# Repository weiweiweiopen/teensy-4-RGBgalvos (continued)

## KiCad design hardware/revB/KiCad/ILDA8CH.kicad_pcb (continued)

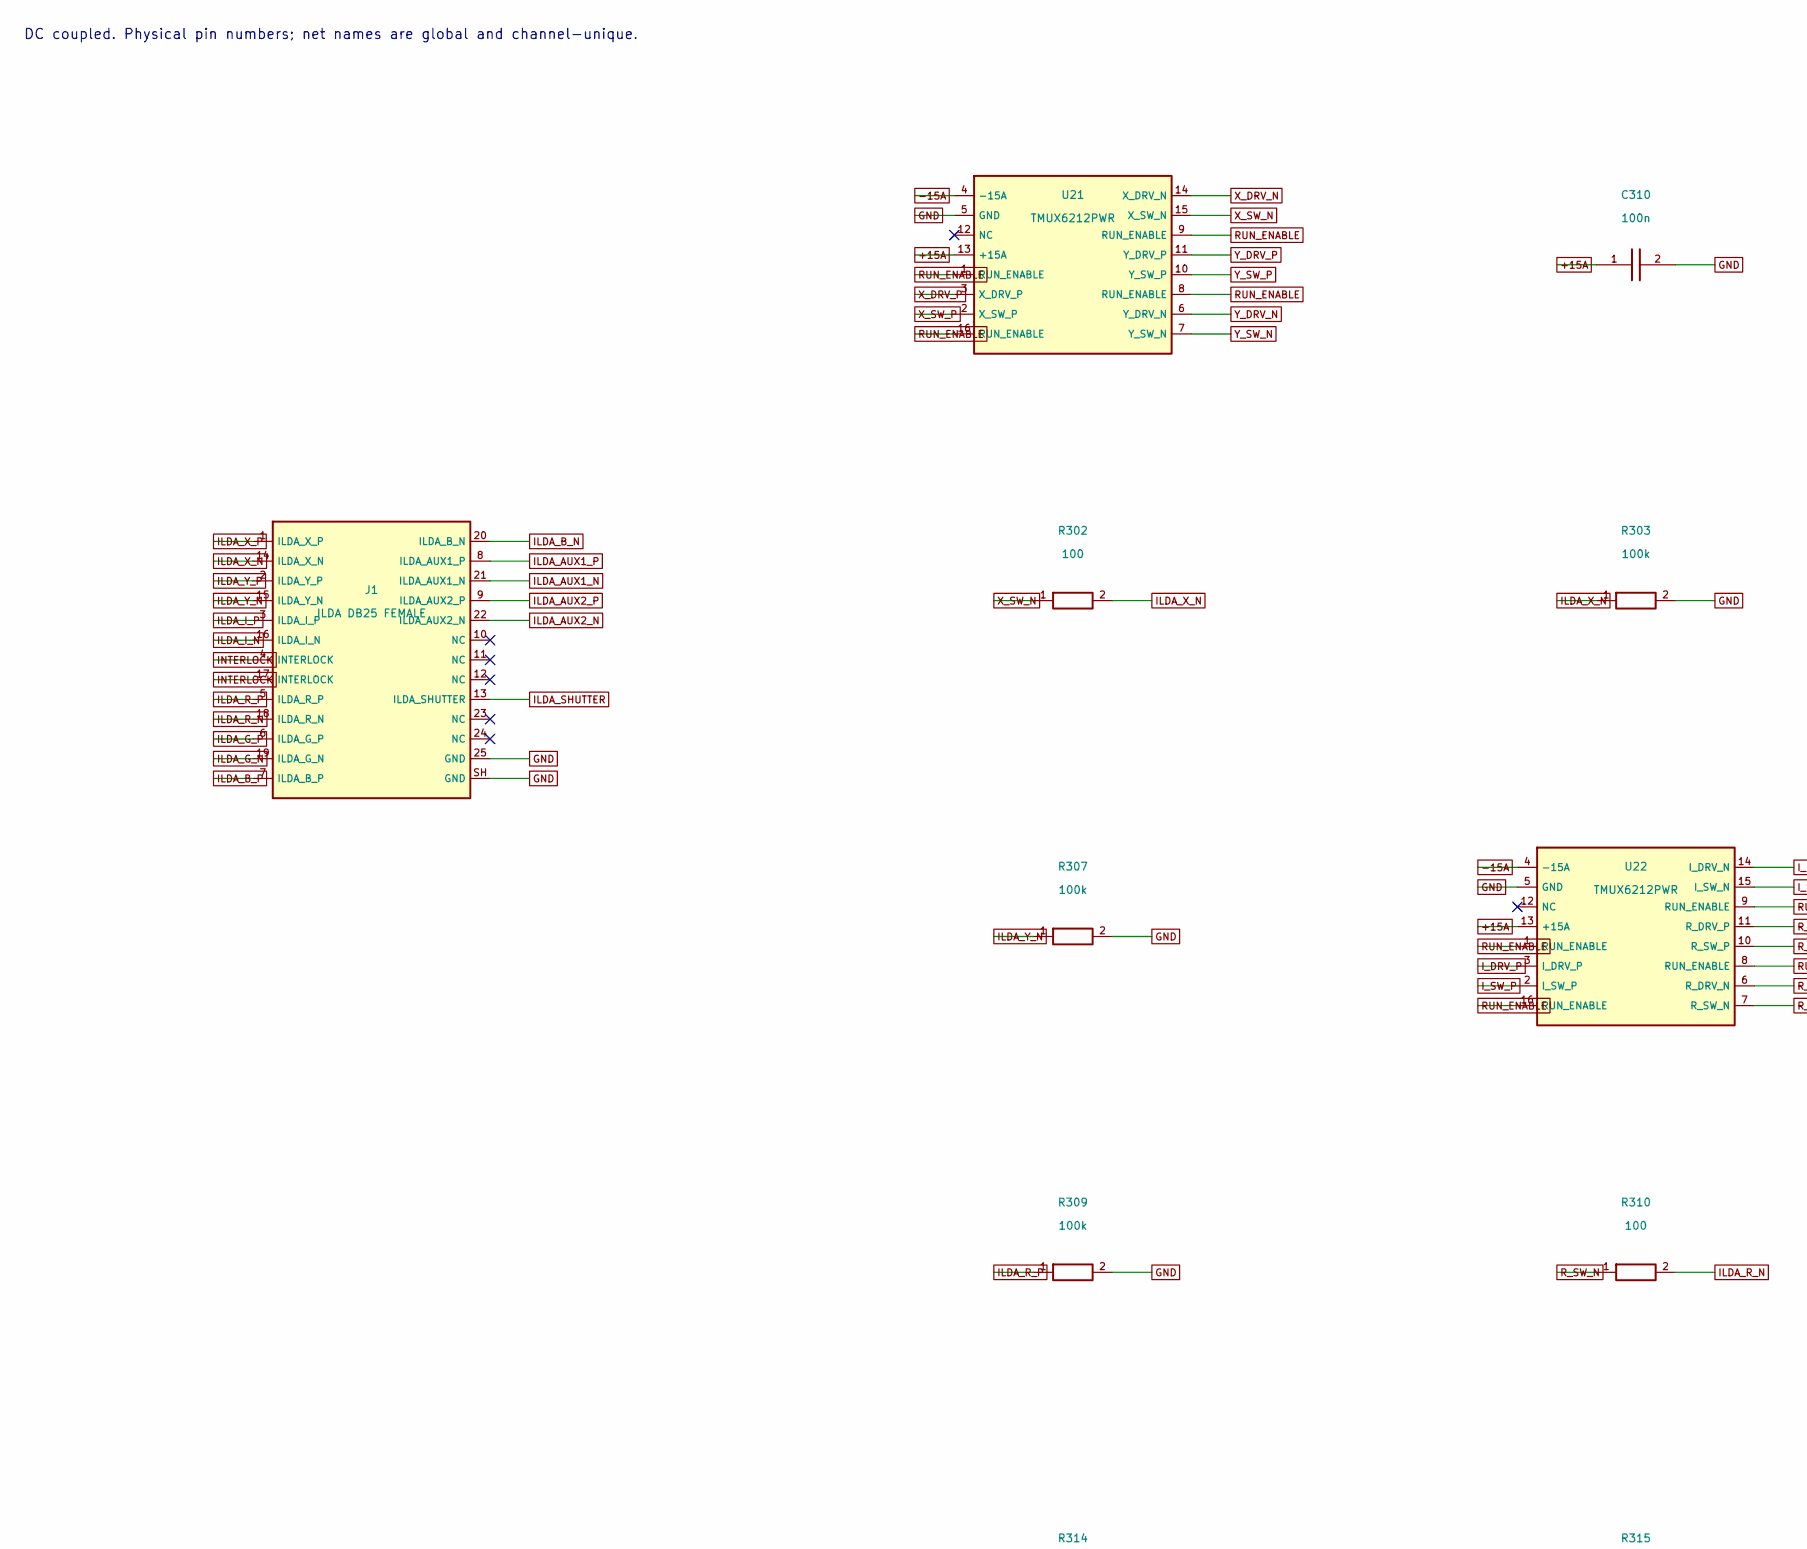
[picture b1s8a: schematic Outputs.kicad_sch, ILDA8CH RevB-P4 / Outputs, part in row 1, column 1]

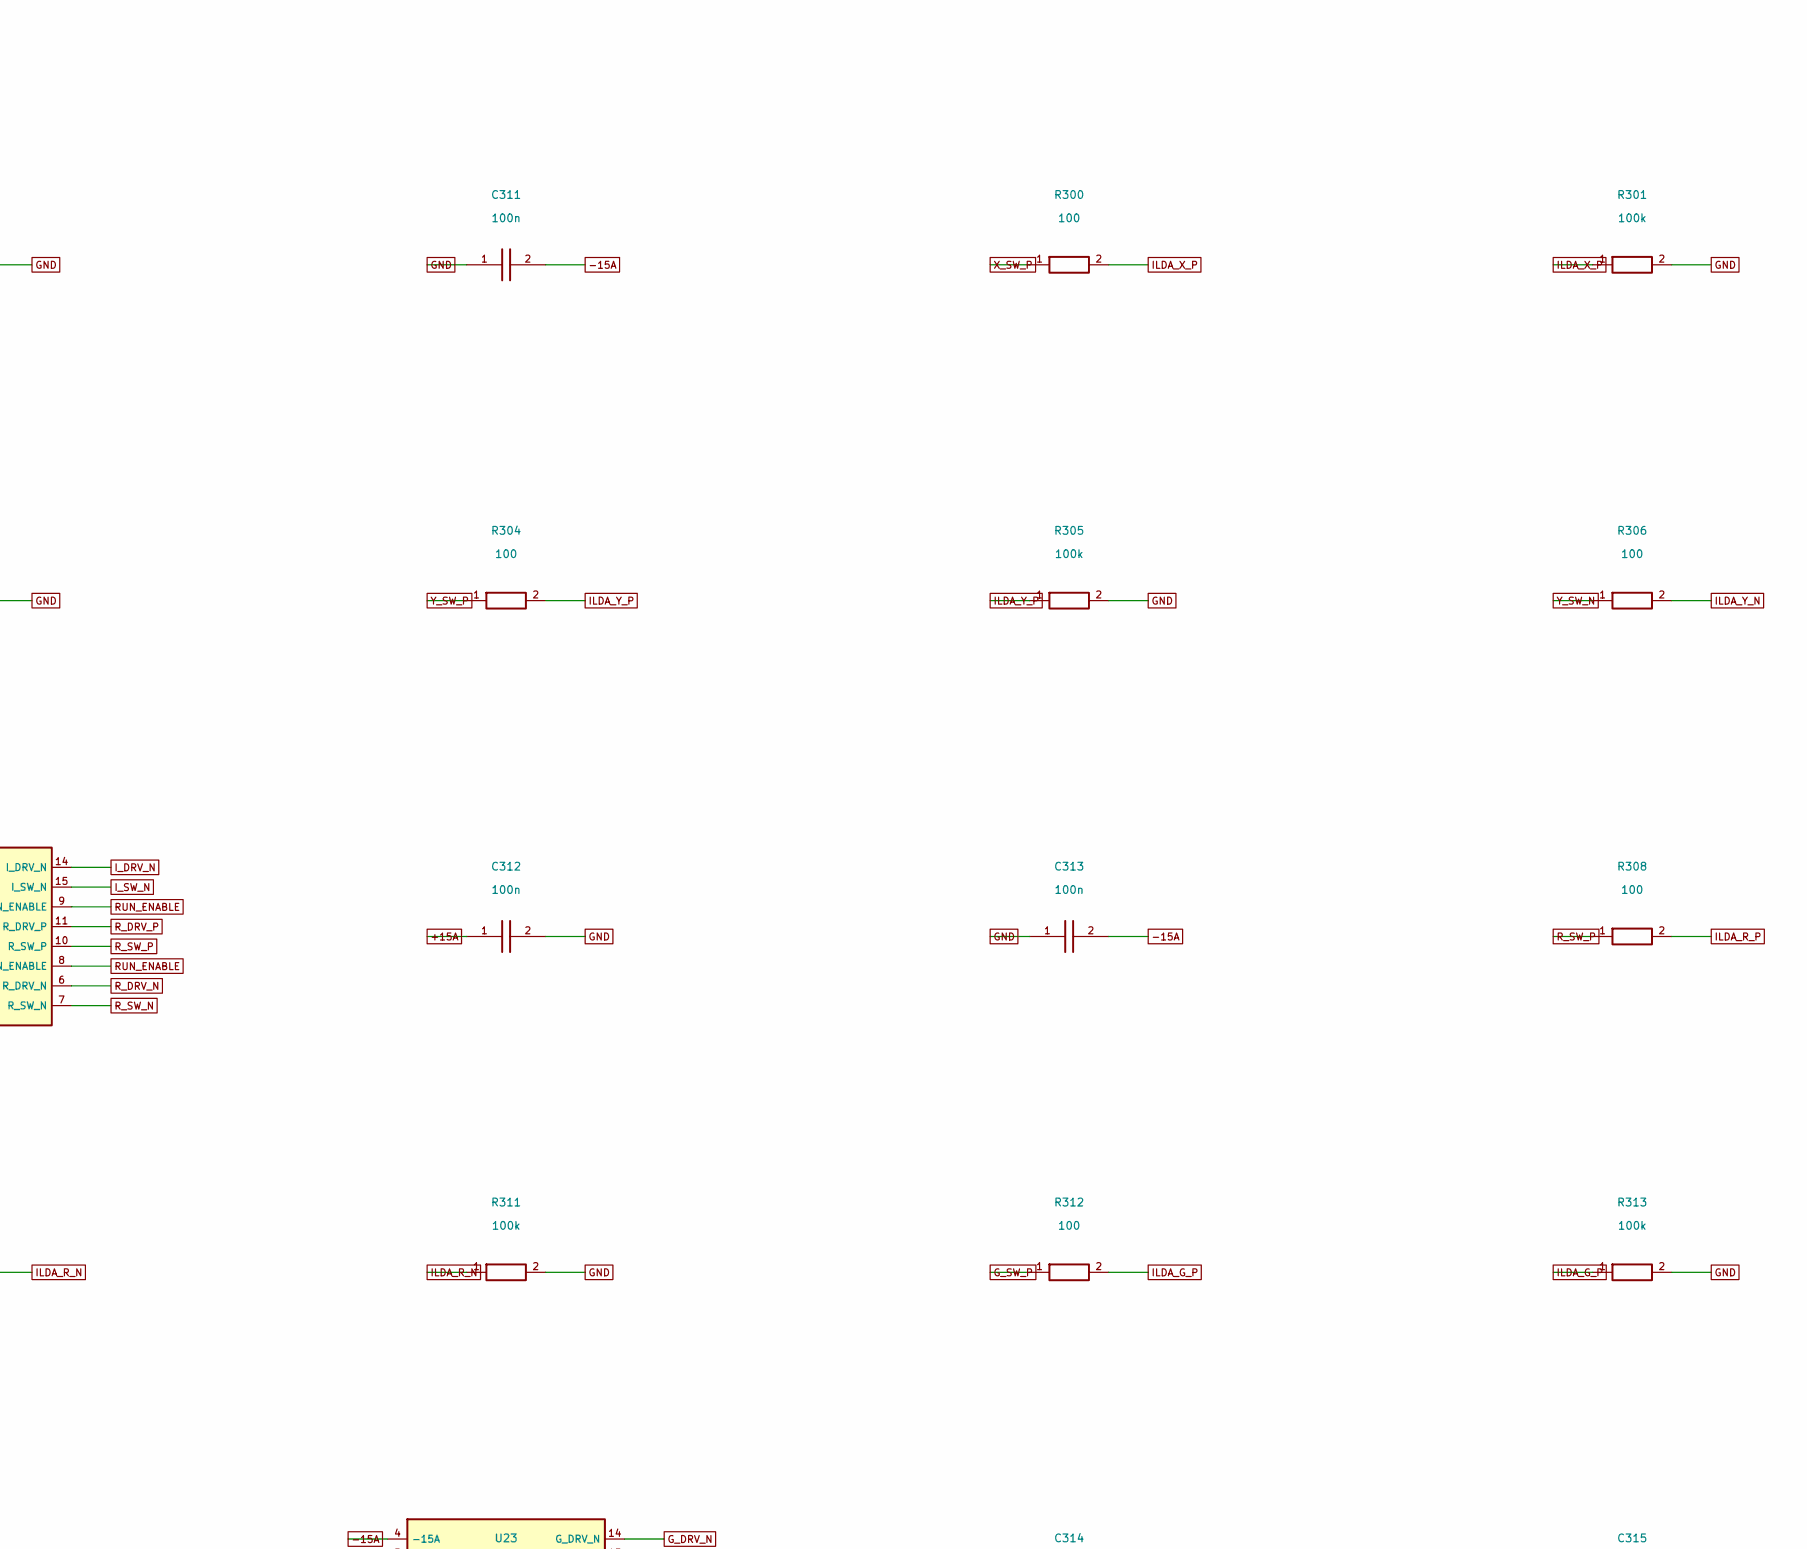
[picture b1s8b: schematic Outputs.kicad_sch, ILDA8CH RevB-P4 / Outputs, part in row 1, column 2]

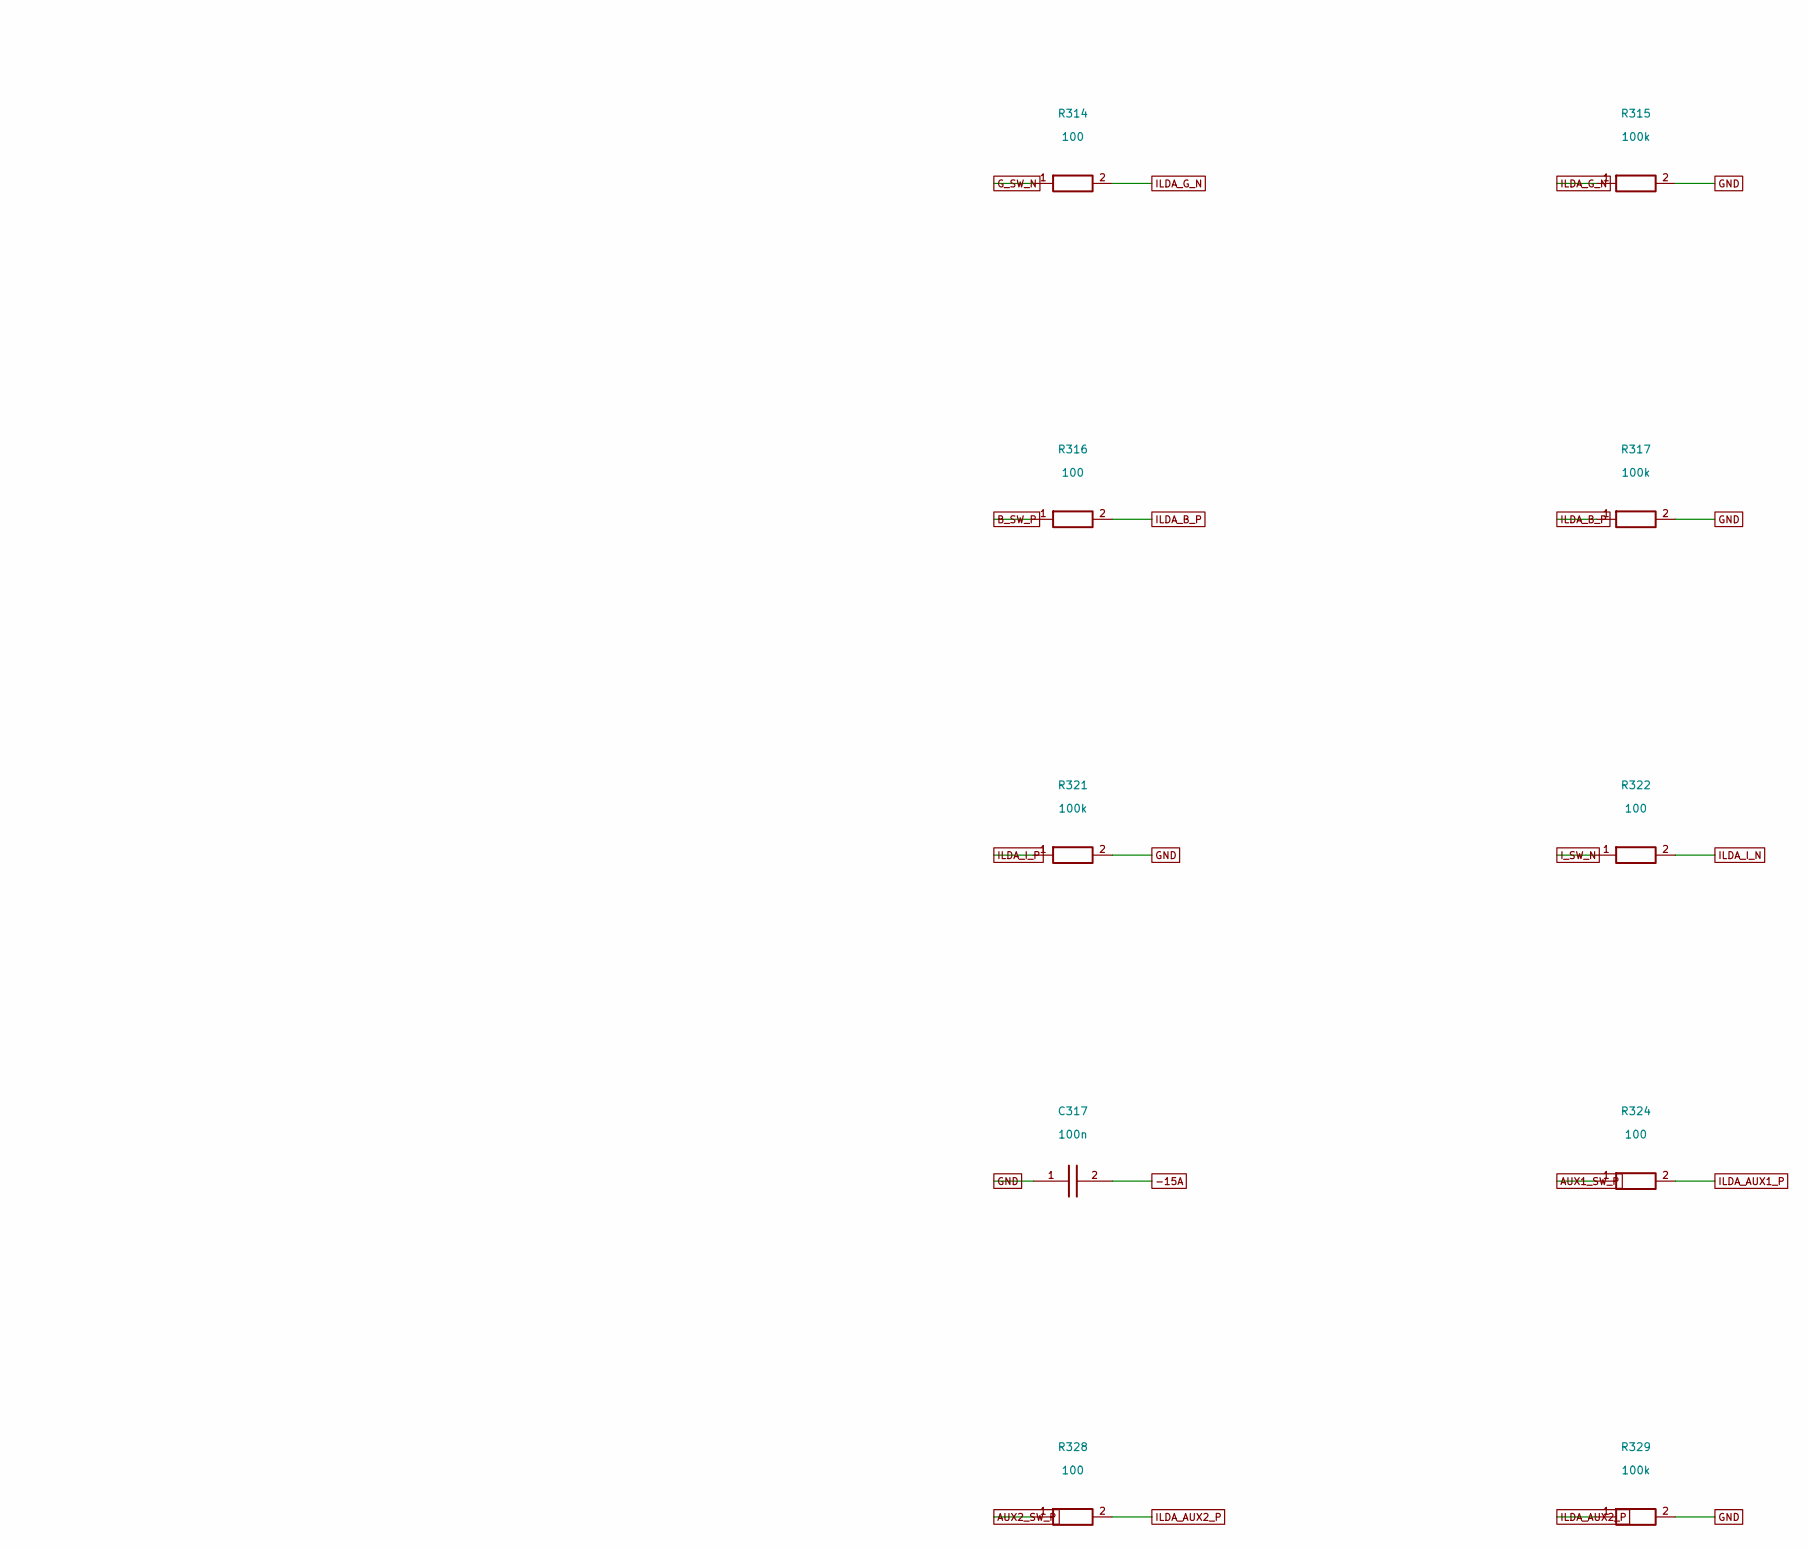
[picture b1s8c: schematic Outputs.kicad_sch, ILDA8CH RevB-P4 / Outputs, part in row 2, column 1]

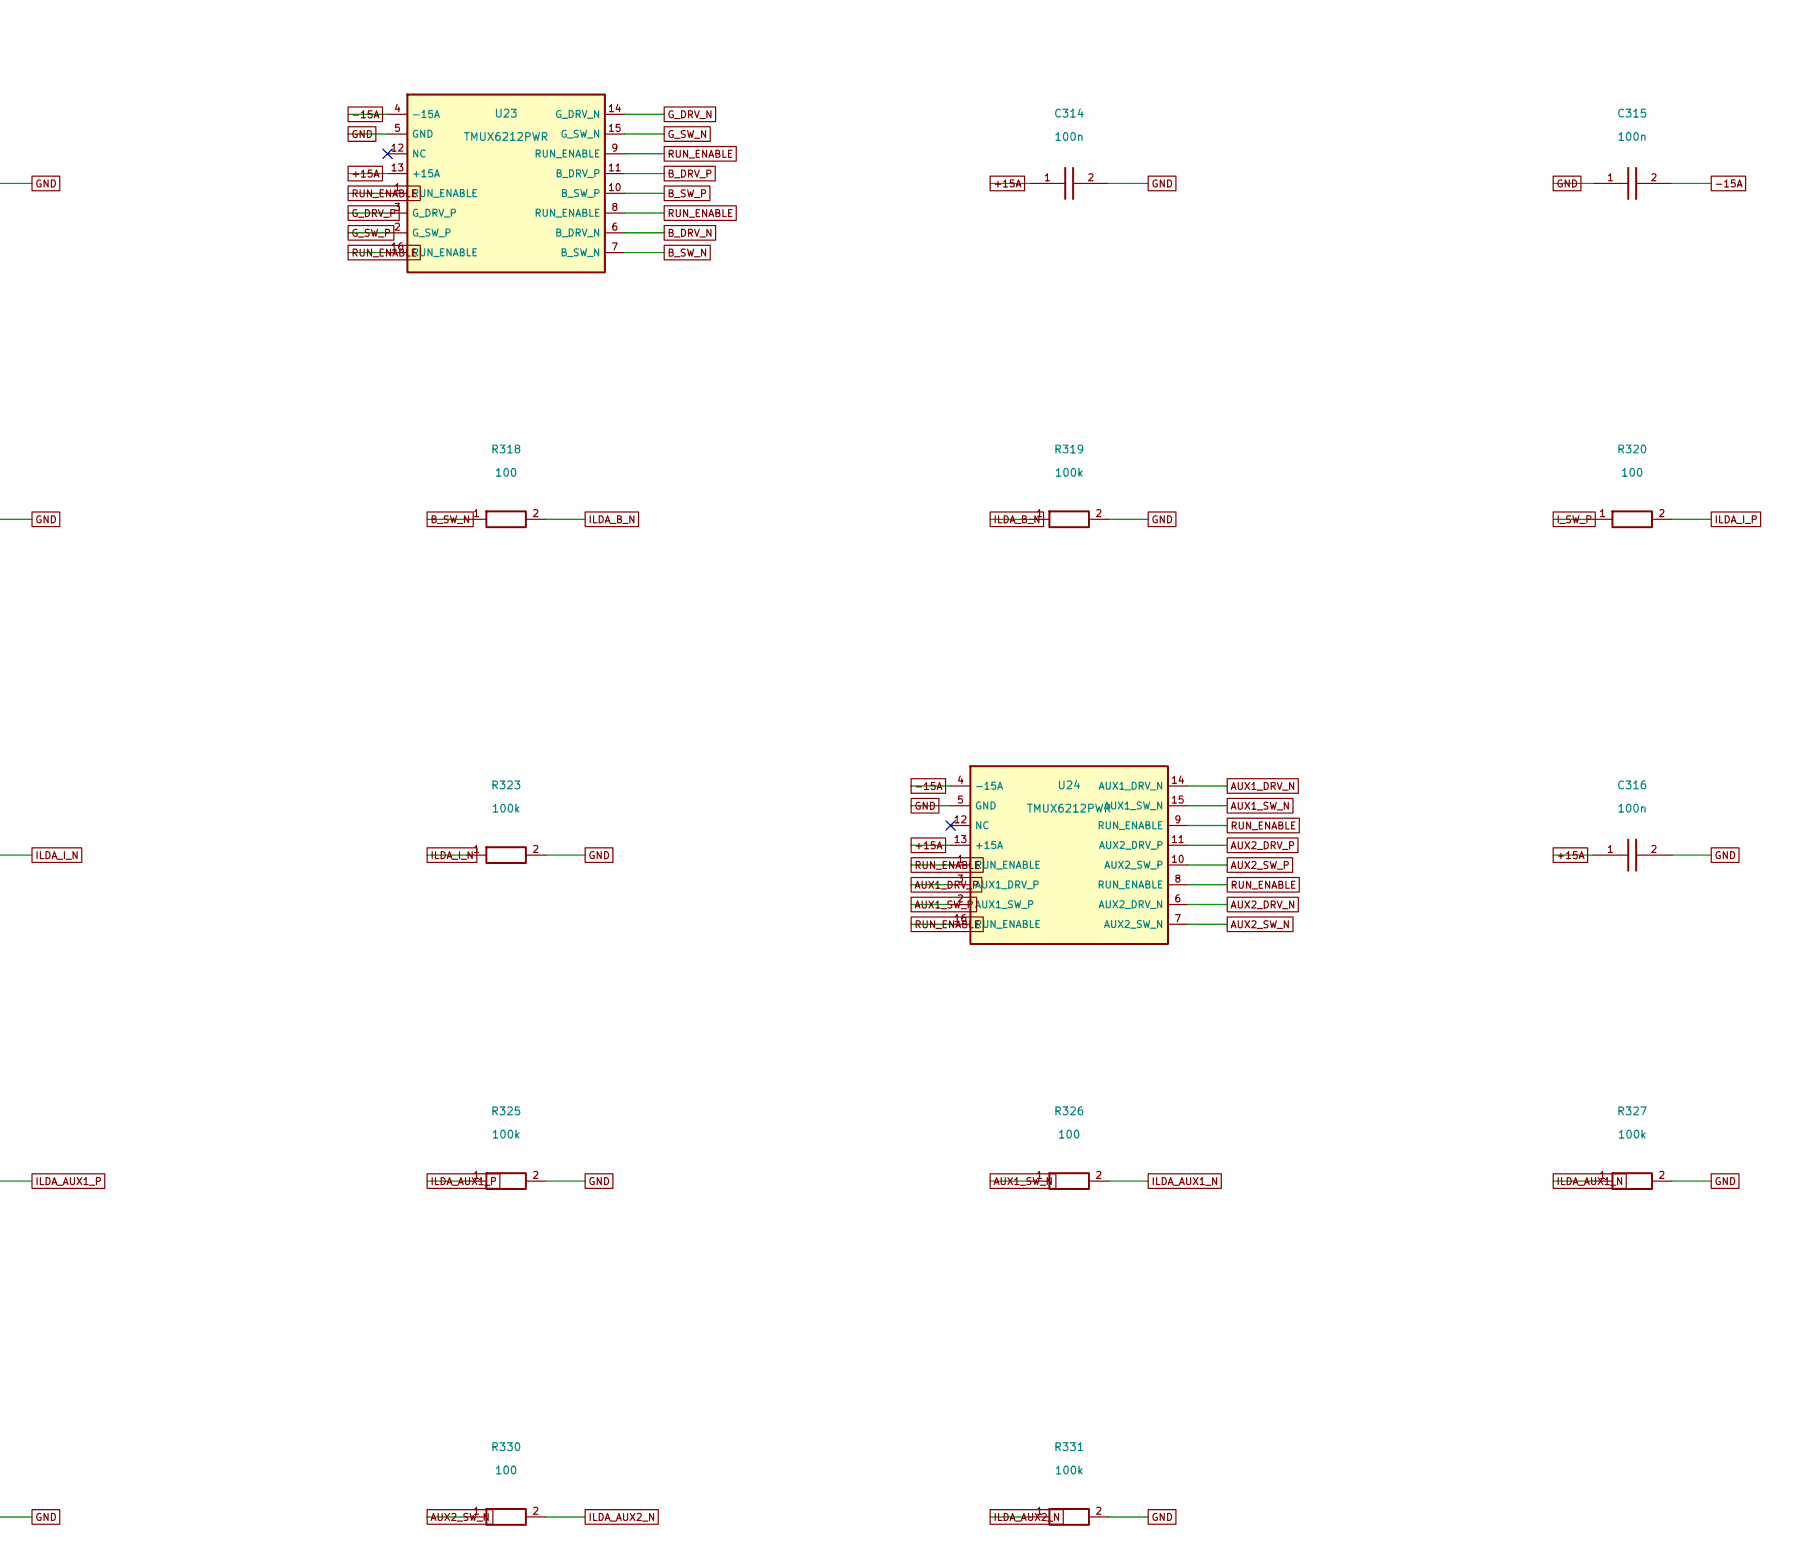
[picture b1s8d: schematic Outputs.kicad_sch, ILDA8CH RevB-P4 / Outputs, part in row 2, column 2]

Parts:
C310, C311, C312, C313, C314, C315, C316, C317: 100n; Capacitor_SMD__C_0603_1608Metric; MPN GRM188R71H104KA93D; LCSC C77055
J1: ILDA DB25 FEMALE; Connector_Dsub__DSUB-25_Socket_Horizontal_P2.77x2.84mm_Edge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; MPN CANDIDATE: RA DB25 female, 7.70mm pin/e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
R300, R302, R304, R306, R308, R310, R312, R314, R316, R318, R320, R322, R324, R326, R328, R330: 100; Resistor_SMD__R_2512_6332Metric; MPN RC2512FK-07100RL; LCSC C309603
R301, R303, R305, R307, R309, R311, R313, R315, R317, R319, R321, R323, R325, R327, R329, R331: 100k; Resistor_SMD__R_0603_1608Metric; MPN RC0603FR-07100KL; LCSC C14675
U21, U22, U23, U24: TMUX6212PWR; Package_SO__TSSOP-16_4.4x5mm_P0.65mm; MPN TMUX6212PWR; LCSC C2902526

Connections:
+15A: C310.1, C312.1, C314.1, C316.1, U21.13 (+15A), U22.13 (+15A), U23.13 (+15A), U24.13 (+15A); also elsewhere on the board
-15A: C311.2, C313.2, C315.2, C317.2, U21.4 (-15A), U22.4 (-15A), U23.4 (-15A), U24.4 (-15A); also elsewhere on the board
AUX1_DRV_N: U24.14 (AUX1_DRV_N); also elsewhere on the board
AUX1_DRV_P: U24.3 (AUX1_DRV_P); also elsewhere on the board
AUX1_SW_N: R326.1, U24.15 (AUX1_SW_N)
AUX1_SW_P: R324.1, U24.2 (AUX1_SW_P)
AUX2_DRV_N: U24.6 (AUX2_DRV_N); also elsewhere on the board
AUX2_DRV_P: U24.11 (AUX2_DRV_P); also elsewhere on the board
AUX2_SW_N: R330.1, U24.7 (AUX2_SW_N)
AUX2_SW_P: R328.1, U24.10 (AUX2_SW_P)
B_DRV_N: U23.6 (B_DRV_N); also elsewhere on the board
B_DRV_P: U23.11 (B_DRV_P); also elsewhere on the board
B_SW_N: R318.1, U23.7 (B_SW_N)
B_SW_P: R316.1, U23.10 (B_SW_P)
GND: C310.2, C311.1, C312.2, C313.1, C314.2, C315.1, C316.2, C317.1, J1.25 (GND), J1.SH (GND), R301.2, R303.2, R305.2, R307.2, R309.2, R311.2, R313.2, R315.2, R317.2, R319.2, R321.2, R323.2, R325.2, R327.2, R329.2, R331.2, U21.5 (GND), U22.5 (GND), U23.5 (GND), U24.5 (GND); also elsewhere on the board
G_DRV_N: U23.14 (G_DRV_N); also elsewhere on the board
G_DRV_P: U23.3 (G_DRV_P); also elsewhere on the board
G_SW_N: R314.1, U23.15 (G_SW_N)
G_SW_P: R312.1, U23.2 (G_SW_P)
ILDA_AUX1_N: J1.21 (ILDA_AUX1_N), R326.2, R327.1
ILDA_AUX1_P: J1.8 (ILDA_AUX1_P), R324.2, R325.1
ILDA_AUX2_N: J1.22 (ILDA_AUX2_N), R330.2, R331.1
ILDA_AUX2_P: J1.9 (ILDA_AUX2_P), R328.2, R329.1
ILDA_B_N: J1.20 (ILDA_B_N), R318.2, R319.1
ILDA_B_P: J1.7 (ILDA_B_P), R316.2, R317.1
ILDA_G_N: J1.19 (ILDA_G_N), R314.2, R315.1
ILDA_G_P: J1.6 (ILDA_G_P), R312.2, R313.1
ILDA_I_N: J1.16 (ILDA_I_N), R322.2, R323.1
ILDA_I_P: J1.3 (ILDA_I_P), R320.2, R321.1
ILDA_R_N: J1.18 (ILDA_R_N), R310.2, R311.1
ILDA_R_P: J1.5 (ILDA_R_P), R308.2, R309.1
ILDA_SHUTTER: J1.13 (ILDA_SHUTTER); also elsewhere on the board
ILDA_X_N: J1.14 (ILDA_X_N), R302.2, R303.1
ILDA_X_P: J1.1 (ILDA_X_P), R300.2, R301.1
ILDA_Y_N: J1.15 (ILDA_Y_N), R306.2, R307.1
ILDA_Y_P: J1.2 (ILDA_Y_P), R304.2, R305.1
INTERLOCK: J1.4 (INTERLOCK), J1.17 (INTERLOCK)
I_DRV_N: U22.14 (I_DRV_N); also elsewhere on the board
I_DRV_P: U22.3 (I_DRV_P); also elsewhere on the board
I_SW_N: R322.1, U22.15 (I_SW_N)
I_SW_P: R320.1, U22.2 (I_SW_P)
RUN_ENABLE: U21.1 (RUN_ENABLE), U21.8 (RUN_ENABLE), U21.9 (RUN_ENABLE), U21.16 (RUN_ENABLE), U22.1 (RUN_ENABLE), U22.8 (RUN_ENABLE), U22.9 (RUN_ENABLE), U22.16 (RUN_ENABLE), U23.1 (RUN_ENABLE), U23.8 (RUN_ENABLE), U23.9 (RUN_ENABLE), U23.16 (RUN_ENABLE), U24.1 (RUN_ENABLE), U24.8 (RUN_ENABLE), U24.9 (RUN_ENABLE), U24.16 (RUN_ENABLE); also elsewhere on the board
R_DRV_N: U22.6 (R_DRV_N); also elsewhere on the board
R_DRV_P: U22.11 (R_DRV_P); also elsewhere on the board
R_SW_N: R310.1, U22.7 (R_SW_N)
R_SW_P: R308.1, U22.10 (R_SW_P)
X_DRV_N: U21.14 (X_DRV_N); also elsewhere on the board
X_DRV_P: U21.3 (X_DRV_P); also elsewhere on the board
X_SW_N: R302.1, U21.15 (X_SW_N)
X_SW_P: R300.1, U21.2 (X_SW_P)
Y_DRV_N: U21.6 (Y_DRV_N); also elsewhere on the board
Y_DRV_P: U21.11 (Y_DRV_P); also elsewhere on the board
Y_SW_N: R306.1, U21.7 (Y_SW_N)
Y_SW_P: R304.1, U21.10 (Y_SW_P)

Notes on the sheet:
DC coupled. Physical pin numbers; net names are global and channel-unique.

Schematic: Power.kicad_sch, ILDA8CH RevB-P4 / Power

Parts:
C1, C2, C3, C4, C5: 10u; Capacitor_SMD__C_0805_2012Metric; MPN GRM21BR61E106KA73L; LCSC C84416
C37, C38, C350: 100n; Capacitor_SMD__C_0603_1608Metric; MPN GRM188R71H104KA93D; LCSC C77055
D1, D2: SS14; Diode_SMD__D_SMA; MPN SS14; LCSC C2480
FB1: 600R@100MHz; Inductor_SMD__L_0805_2012Metric; MPN BLM21PG601SN1D; LCSC C41556732
FID1, FID2, FID3: FIDUCIAL; Fiducial__Fiducial_1mm_Mask2mm
H1, H2, H3, H4: M3 NPTH; MountingHole__MountingHole_3.2mm_M3
J2: Molex KK-254 3P +/-15V; Connector_Molex__Molex_KK-254_AE-6410-03A_1x03_P2.54mm_Vert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; MPN 22-27-2031
R23, R25, R352, R354, R357, R358, R360, R369, R370: 100k; Resistor_SMD__R_0603_1608Metric; MPN RC0603FR-07100KL; LCSC C14675
R24: 20k; Resistor_SMD__R_0603_1608Metric; MPN RT0603BRD0720KL; LCSC C723637
R26: 10k; Resistor_SMD__R_0603_1608Metric; MPN RT0603BRD0710KL; LCSC C95204
R350, R356: 1M; Resistor_SMD__R_0603_1608Metric; MPN RC0603FR-071ML; LCSC C105578
R351: 200k; Resistor_SMD__R_0603_1608Metric; MPN RC0603FR-07200KL; LCSC C105574
R353: 150k; Resistor_SMD__R_0603_1608Metric; MPN RC0603FR-07150KL; LCSC C114660
R355, R361: 10M; Resistor_SMD__R_0603_1608Metric; MPN RC0603FR-0710ML; LCSC C114606
R359: 45.3k; Resistor_SMD__R_0603_1608Metric; MPN RC0603FR-0745K3L; LCSC C245971
R367: 1k; Resistor_SMD__R_0603_1608Metric; MPN RT0603BRD071KL; LCSC C110776
R371, R372: 100; Resistor_SMD__R_0603_1608Metric; MPN RC0603FR-07100RL; LCSC C105588
U2: TLV75533PDBVR; Package_TO_SOT_SMD__SOT-23-5; MPN TLV75533PDBVR; LCSC C404027
U6: TLV3202AIDGKR; TI_DGK0008A_VSSOP8_3x3_P0.65_Land1.4x0.45; MPN TLV3202AIDGKR; LCSC C478075

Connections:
+3V3: C2.1, U2.5 (+3V3); also elsewhere on the board
+5VA: C3.1, FB1.2; also elsewhere on the board
+15A: C4.1, D1.1 (K), R23.1, R350.1; also elsewhere on the board
-15A: C5.2, D2.2 (A), R25.1, R356.1; also elsewhere on the board
GND: C1.2, C2.2, C3.2, C4.2, C5.1, C37.2, C38.2, C350.2, J2.2 (GND), R24.2, R351.2, R354.2, R360.2, R367.2, R369.2, R370.2, U2.2 (GND), U6.4 (GND); also elsewhere on the board
MCU_3V3: R26.2; also elsewhere on the board
N15_IN: D2.1 (K), J2.3 (N15_IN)
NMON: R358.2, U6.6 (IN2-)
NMON_RAW: R356.2, R357.1, R358.1
NREF: R359.2, R360.1, R361.2, U6.5 (IN2+)
P15_IN: D1.2 (A), J2.1 (P15_IN)
PMON: R352.2, U6.3 (IN1+)
PMON_RAW: R350.2, R351.1, R352.1, R355.2
PREF: R353.2, R354.1, U6.2 (IN1-)
RAIL_N_GOOD: R370.1, R372.2; also elsewhere on the board
RAIL_N_RAW: R361.1, R372.1, U6.7 (OUT2)
RAIL_P_GOOD: R369.1, R371.2; also elsewhere on the board
RAIL_P_RAW: R355.1, R371.1, U6.1 (OUT1)
SENSE_N15: C38.1, R25.2, R26.1; also elsewhere on the board
SENSE_P15: C37.1, R23.2, R24.1; also elsewhere on the board
USB_5V: C1.1, C350.1, FB1.1, R353.1, R357.2, R359.1, R367.1, U2.1 (USB_5V), U2.3 (USB_5V), U6.8 (VCC); also elsewhere on the board

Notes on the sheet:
DC coupled. Physical pin numbers; net names are global and channel-unique.

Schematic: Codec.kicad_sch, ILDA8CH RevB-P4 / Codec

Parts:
C7, C8, C9, C10, C11, C12, C13, C17, C19, C21, C355, C356, C357, C358: 100n; Capacitor_SMD__C_0603_1608Metric; MPN GRM188R71H104KA93D; LCSC C77055
C14, C15: 10u; Capacitor_SMD__C_0805_2012Metric; MPN GRM21BR61E106KA73L; LCSC C84416
C16, C22, C23, C24, C25, C26, C27, C28, C29, C30, C31, C32, C33: 4.7u; Capacitor_SMD__C_0805_2012Metric; MPN GRM21BR61E475KA12L; LCSC C77077
C18: 22u; Capacitor_SMD__C_1206_3216Metric; MPN GRM31CR61E226KE15L; LCSC C77091
C20: 100u; Capacitor_SMD__C_1210_3225Metric; MPN GRM32ER61A107ME20L; LCSC C84455
R8, R9, R10, R11, R12, R13, R14, R15: 10k; Resistor_SMD__R_0603_1608Metric; MPN RT0603BRD0710KL; LCSC C95204
R16: 100k; Resistor_SMD__R_0603_1608Metric; MPN RC0603FR-07100KL; LCSC C14675
U1: CS42448-CQZR; Package_QFP__LQFP-64_10x10mm_P0.5mm; MPN CS42448-CQZR; LCSC C2151089
U31, U32, U33, U34: ADG4613BRUZ; Package_SO__TSSOP-16_4.4x5mm_P0.65mm; MPN ADG4613BRUZ; LCSC C657392

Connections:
+3V3: C7.1, C8.1, C9.1, C10.1, C11.1, C14.1, R15.2, U1.4 (VLC), U1.6 (VD), U1.8 (VLS), U1.24 (VD); also elsewhere on the board
+5VA: C12.1, C13.1, C15.1, R16.2, U1.44 (VA), U1.53 (VA); also elsewhere on the board
AD0: R8.1, U1.1 (AD0)
AD1: R9.1, U1.2 (AD1)
AIN1: C22.1, U1.46 (AIN1)
AIN2: C23.1, U1.45 (AIN2)
AIN3: C24.1, U1.48 (AIN3)
AIN4: C25.1, U1.47 (AIN4)
AIN5: C26.1, U1.50 (AIN5)
AIN6: C27.1, U1.49 (AIN6)
AIN7: C28.1, U1.52 (AIN7)
AIN8: C29.1, U1.51 (AIN8)
AIN9: C30.1, U1.58 (AIN9)
AIN10: C31.1, U1.57 (AIN10)
AIN11: C32.1, U1.60 (AIN11)
AIN12: C33.1, U1.59 (AIN12)
AUX_SDIN: R11.1, U1.22 (AUX_SDIN)
BCLK: U1.9 (ADC_SCLK), U1.18 (DAC_SCLK); also elsewhere on the board
CODEC_INT: R15.1, U1.61 (INT); also elsewhere on the board
CODEC_RESET: R10.1, U1.3 (~RST), U31.1 (IN1), U31.8 (IN4), U32.1 (IN1), U32.8 (IN4), U33.1 (IN1), U33.8 (IN4), U34.1 (IN1), U34.8 (IN4); also elsewhere on the board
DAC1_N: U1.25 (DAC1_N), U31.14 (S2)
DAC1_P: U1.26 (DAC1_P), U31.3 (S1)
DAC2_N: U1.28 (DAC2_N), U31.6 (S4)
DAC2_P: U1.27 (DAC2_P), U31.11 (S3)
DAC3_N: U1.29 (DAC3_N), U32.14 (S2)
DAC3_P: U1.30 (DAC3_P), U32.3 (S1)
DAC4_N: U1.32 (DAC4_N), U32.6 (S4)
DAC4_P: U1.31 (DAC4_P), U32.11 (S3)
DAC5_N: U1.33 (DAC5_N), U33.14 (S2)
DAC5_P: U1.34 (DAC5_P), U33.3 (S1)
DAC6_N: U1.37 (DAC6_N), U33.6 (S4)
DAC6_P: U1.36 (DAC6_P), U33.11 (S3)
DAC7_N: U1.38 (DAC7_N), U34.14 (S2)
DAC7_P: U1.39 (DAC7_P), U34.3 (S1)
DAC8_N: U1.41 (DAC8_N), U34.6 (S4)
DAC8_P: U1.40 (DAC8_P), U34.11 (S3)
DAC_ISOLATE_N: U31.9 (IN3), U31.16 (IN2), U32.9 (IN3), U32.16 (IN2), U33.9 (IN3), U33.16 (IN2), U34.9 (IN3), U34.16 (IN2); also elsewhere on the board
FILT_ADC: C18.1, C21.1, U1.55 (FILT_ADC)
FILT_DAC: C19.1, C20.1, U1.54 (FILT_DAC)
GND: C7.2, C8.2, C9.2, C10.2, C11.2, C12.2, C13.2, C14.2, C15.2, C16.2, C17.2, C18.2, C19.2, C20.2, C21.2, C22.2, C23.2, C24.2, C25.2, C26.2, C27.2, C28.2, C29.2, C30.2, C31.2, C32.2, C33.2, C355.2, C356.2, C357.2, C358.2, R8.2, R9.2, R10.2, R11.2, R12.2, R13.2, R14.2, U1.7 (DGND), U1.23 (DGND), U1.42 (AGND), U1.56 (AGND), U1.62 (DGND), U31.4 (VSS), U31.5 (GND), U32.4 (VSS), U32.5 (GND), U33.4 (VSS), U33.5 (GND), U34.4 (VSS), U34.5 (GND); also elsewhere on the board
ISO_DAC1_N: U31.15 (D2); also elsewhere on the board
ISO_DAC1_P: U31.2 (D1); also elsewhere on the board
ISO_DAC2_N: U31.7 (D4); also elsewhere on the board
ISO_DAC2_P: U31.10 (D3); also elsewhere on the board
ISO_DAC3_N: U32.15 (D2); also elsewhere on the board
ISO_DAC3_P: U32.2 (D1); also elsewhere on the board
ISO_DAC4_N: U32.7 (D4); also elsewhere on the board
ISO_DAC4_P: U32.10 (D3); also elsewhere on the board
ISO_DAC5_N: U33.15 (D2); also elsewhere on the board
ISO_DAC5_P: U33.2 (D1); also elsewhere on the board
ISO_DAC6_N: U33.7 (D4); also elsewhere on the board
ISO_DAC6_P: U33.10 (D3); also elsewhere on the board
ISO_DAC7_N: U34.15 (D2); also elsewhere on the board
ISO_DAC7_P: U34.2 (D1); also elsewhere on the board
ISO_DAC8_N: U34.7 (D4); also elsewhere on the board
ISO_DAC8_P: U34.10 (D3); also elsewhere on the board
LRCLK: U1.5 (ADC_LRCK), U1.19 (DAC_LRCK); also elsewhere on the board
MCLK: U1.10 (MCLK); also elsewhere on the board
MUTEC_5V: R16.1, U1.35 (MUTEC); also elsewhere on the board
SCL: U1.63 (SCL); also elsewhere on the board
SDA: U1.64 (SDA); also elsewhere on the board
SDIN2: R12.1, U1.16 (DAC_SDIN2)
SDIN3: R13.1, U1.15 (DAC_SDIN3)
SDIN4: R14.1, U1.14 (DAC_SDIN4)
TDM_TX: U1.17 (DAC_SDIN1); also elsewhere on the board
USB_5V: C355.1, C356.1, C357.1, C358.1, U31.13 (VDD), U32.13 (VDD), U33.13 (VDD), U34.13 (VDD); also elsewhere on the board
VQ: C16.1, C17.1, U1.43 (VQ); also elsewhere on the board

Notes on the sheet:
DC coupled. Physical pin numbers; net names are global and channel-unique.

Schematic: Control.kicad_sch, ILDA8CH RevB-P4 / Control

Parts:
A1: Teensy 4.0; Teensy40_Socket; MPN TEENSY40
C6, C34, C35, C36, C351, C352, C353, C354, C359, C360, C361: 100n; Capacitor_SMD__C_0603_1608Metric; MPN GRM188R71H104KA93D; LCSC C77055
R1, R2, R3, R4, R5: 100; Resistor_SMD__R_0603_1608Metric; MPN RC0603FR-07100RL; LCSC C105588
R6, R7, R18, R19, R373: 2.2k; Resistor_SMD__R_0603_1608Metric; MPN RC0603FR-072K2L; LCSC C114662
R17, R22, R368: 100k; Resistor_SMD__R_0603_1608Metric; MPN RC0603FR-07100KL; LCSC C14675
R20, R362, R363: 10k; Resistor_SMD__R_0603_1608Metric; MPN RT0603BRD0710KL; LCSC C95204
R21: 1k; Resistor_SMD__R_0603_1608Metric; MPN RT0603BRD071KL; LCSC C110776
R364, R365: 4.7k; Resistor_SMD__R_0603_1608Metric; MPN RT0603BRD074K7L; LCSC C513565
R366: 330; Resistor_SMD__R_0603_1608Metric; MPN RC0603FR-07330RL; LCSC C105881
TP1: GND; TestPoint__TestPoint_Pad_D1.0mm
TP2: +3V3; TestPoint__TestPoint_Pad_D1.0mm
TP3: +5VA; TestPoint__TestPoint_Pad_D1.0mm
TP4: +15A; TestPoint__TestPoint_Pad_D1.0mm
TP5: -15A; TestPoint__TestPoint_Pad_D1.0mm
TP6: RUN_ENABLE; TestPoint__TestPoint_Pad_D1.0mm
TP7: MCLK; TestPoint__TestPoint_Pad_D1.0mm
TP8: LRCLK; TestPoint__TestPoint_Pad_D1.0mm
TP9: BCLK; TestPoint__TestPoint_Pad_D1.0mm
TP10: TDM_TX; TestPoint__TestPoint_Pad_D1.0mm
TP11: VQ; TestPoint__TestPoint_Pad_D1.0mm
U3: SN74LVC1G17DBVR; Package_TO_SOT_SMD__SOT-23-5; MPN SN74LVC1G17DBVR; LCSC C7836
U4: CD74HC123M96; Package_SO__SOIC-16_3.9x9.9mm_P1.27mm; MPN CD74HC123M96; LCSC C133784
U5: SN74AHCT1G125DBVR; Package_TO_SOT_SMD__SOT-23-5; MPN SN74AHCT1G125DBVR; LCSC C7484
U7: SN74LVC1G11DBVR; Package_TO_SOT_SMD__SOT-23-6; MPN SN74LVC1G11DBVR; LCSC C22046
U8: SN74LVC1G175DBVR; Package_TO_SOT_SMD__SOT-23-6; MPN SN74LVC1G175DBVR; LCSC C128412
U9: SN74LVC1G06DBVR; Package_TO_SOT_SMD__SOT-23-5; MPN SN74LVC1G06DBVR; LCSC C840103
U10: TPS3839K33DBZR; Package_TO_SOT_SMD__SOT-23; MPN TPS3839K33DBZR; LCSC C96333
U35: ADG4613BRUZ; Package_SO__TSSOP-16_4.4x5mm_P0.65mm; MPN ADG4613BRUZ; LCSC C657392
U36: SN74LVC1G08DBVR; Package_TO_SOT_SMD__SOT-23-5; MPN SN74LVC1G08DBVR; LCSC C7666
U37: SN74AHCT1G14DBVR; Package_TO_SOT_SMD__SOT-23-5; MPN SN74AHCT1G14DBVR; LCSC C55250

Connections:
+3V3: C6.1, C35.1, C351.1, C352.1, C353.1, R6.2, R7.2, R17.1, TP2.1, U3.5 (+3V3), U4.16 (VCC), U7.5 (VCC), U8.3 (D), U8.5 (VCC), U9.5 (VCC); also elsewhere on the board
+5VA: TP3.1; also elsewhere on the board
+15A: TP4.1; also elsewhere on the board
-15A: TP5.1; also elsewhere on the board
ADC_N15: A1.17 (ADC_N15), R365.1, U35.7 (D4)
ADC_P15: A1.16 (ADC_P15), R364.1, U35.2 (D1)
ARM: A1.8 (ARM), R18.1, U8.1 (CLK)
ARM_QUALIFIED: U4.3 (~1RD), U8.4 (Q)
BCLK: R3.2, TP9.1; also elsewhere on the board
BCLK_GPIO: A1.23 (BCLK_GPIO), R3.1
CODEC_INT: A1.5 (CODEC_INT); also elsewhere on the board
CODEC_RESET: R5.2, U8.6 (~CLR), U9.2 (A), U37.2 (A); also elsewhere on the board
CODEC_RESET_GPIO: A1.4 (CODEC_RESET_GPIO), R373.1, U7.1 (A)
DAC_ISOLATE_N: R363.2, U9.4 (Y_OD); also elsewhere on the board
GND: A1.1 (GND), A1.27 (GND), C6.2, C35.2, C36.2, C351.2, C352.2, C353.2, C354.2, C359.2, C360.2, C361.2, R18.2, R19.2, R20.2, R22.2, R362.2, R364.2, R365.2, R366.2, R368.2, R373.2, TP1.1, U3.3 (GND), U4.1 (1A), U4.8 (GND), U4.9 (2A), U4.10 (2B), U4.11 (~2RD), U5.3 (GND), U7.2 (GND), U8.2 (GND), U9.3 (GND), U10.1 (GND), U35.4 (VSS), U35.5 (GND), U35.10 (D3), U35.11 (S3), U35.14 (S2), U35.15 (D2), U36.3 (GND), U37.3 (GND); also elsewhere on the board
HEARTBEAT: A1.6 (HEARTBEAT), R19.1, U4.2 (1B)
ILDA_SHUTTER: R21.2, R22.1; also elsewhere on the board
LRCLK: R2.2, TP8.1; also elsewhere on the board
LRCLK_GPIO: A1.22 (LRCLK_GPIO), R2.1
MCLK: R4.2, TP7.1; also elsewhere on the board
MCLK_GPIO: A1.25 (MCLK_GPIO), R4.1
MCU_3V3: A1.26 (MCU_3V3), C354.1, C359.1, C360.1, R366.1, U10.3 (VDD), U35.9 (IN3), U35.13 (VDD), U35.16 (IN2), U36.5 (VCC); also elsewhere on the board
MCU_POWER_GOOD: R368.1, U10.2 (RESET_N), U35.1 (IN1), U35.8 (IN4)
MUTEC_3V3: A1.11 (MUTEC_3V3), U3.4 (MUTEC_3V3)
MUTEC_5V: U3.2 (MUTEC_5V); also elsewhere on the board
RAILS_GOOD: A1.7 (RAILS_GOOD), R362.1, U36.4 (Y)
RAIL_N_GOOD: U7.6 (C), U36.2 (B); also elsewhere on the board
RAIL_P_GOOD: U7.3 (B), U36.1 (A); also elsewhere on the board
RESET_QUALIFIED: R5.1, U7.4 (Y)
RUN_ENABLE: R20.1, TP6.1, U4.13 (1Q), U5.2 (RUN_ENABLE); also elsewhere on the board
SCL: A1.18 (SCL), R6.1; also elsewhere on the board
SDA: A1.19 (SDA), R7.1; also elsewhere on the board
SENSE_N15: U35.6 (S4); also elsewhere on the board
SENSE_P15: U35.3 (S1); also elsewhere on the board
SHUTTER_DISABLE: U5.1 (SHUTTER_DISABLE), U37.4 (Y)
SHUTTER_DRV: R21.1, U5.4 (SHUTTER_DRV)
TDM_TX: R1.2, TP10.1; also elsewhere on the board
TDM_TX_GPIO: A1.9 (TDM_TX_GPIO), R1.1
USB_5V: A1.28 (USB_5V), C36.1, C361.1, R363.1, U5.5 (USB_5V), U37.5 (VCC); also elsewhere on the board
VQ: TP11.1; also elsewhere on the board
WD_CAP: C34.1, U4.14 (1CEXT)
WD_RC: C34.2, R17.2, U4.15 (1REXT)

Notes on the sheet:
DC coupled. Physical pin numbers; net names are global and channel-unique.

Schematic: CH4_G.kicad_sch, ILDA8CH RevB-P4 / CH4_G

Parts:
C181, C182: 4.7n; Capacitor_SMD__C_0603_1608Metric; MPN GRM1885C1H472JA01D; LCSC C85980
C183, C184: 100n; Capacitor_SMD__C_0603_1608Metric; MPN GRM188R71H104KA93D; LCSC C77055
C185, C186: 4.7u; Capacitor_SMD__C_0805_2012Metric; MPN GRM21BR61E475KA12L; LCSC C77077
R181, R182: 1k; Resistor_SMD__R_0603_1608Metric; MPN RT0603BRD071KL; LCSC C110776
R183, R184, R185, R186: 20k; Resistor_SMD__R_0603_1608Metric; MPN RT0603BRD0720KL; LCSC C723637
R187, R188: 10k; Resistor_SMD__R_0603_1608Metric; MPN RT0603BRD0710KL; LCSC C95204
R189, R190: 100k; Resistor_SMD__R_0603_1608Metric; MPN RC0603FR-07100KL; LCSC C14675
R407, R408: 10M; Resistor_SMD__R_0603_1608Metric; MPN RC0603FR-0710ML; LCSC C114606
U14: OPA4197IDR; Package_SO__SOIC-14_3.9x8.7mm_P1.27mm; MPN OPA4197IDR; LCSC C2058532

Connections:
+15A: C183.1, C185.1, U14.4 (V+); also elsewhere on the board
-15A: C184.2, C186.2, U14.11 (V-); also elsewhere on the board
B4N: R182.1, U14.6 (-), U14.7 (OUT)
B4P: R181.1, U14.1 (OUT), U14.2 (-)
F4N: C182.1, R182.2, R185.1
F4P: C181.1, R181.2, R183.1
GND: C181.2, C182.2, C183.2, C184.1, C185.2, C186.1, R184.2, R407.2, R408.2, U14.12 (+); also elsewhere on the board
G_DRV_N: R188.1, U14.14 (OUT); also elsewhere on the board
G_DRV_P: R186.1, R187.1, U14.8 (OUT); also elsewhere on the board
IN4N: R190.2, R408.1, U14.5 (+)
IN4P: R189.2, R407.1, U14.3 (+)
INV4: R187.2, R188.2, U14.13 (-)
ISO_DAC4_N: R190.1; also elsewhere on the board
ISO_DAC4_P: R189.1; also elsewhere on the board
SUM4N: R185.2, R186.2, U14.9 (-)
SUM4P: R183.2, R184.1, U14.10 (+)

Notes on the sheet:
DC coupled. Physical pin numbers; net names are global and channel-unique.
X/Y DC gain = 39k/(20k+1k); colour gain = 20k/(20k+1k). Calibrate in firmware.
A/B: unity-gain input buffers. C: matched subtractor. D: complementary driver.
